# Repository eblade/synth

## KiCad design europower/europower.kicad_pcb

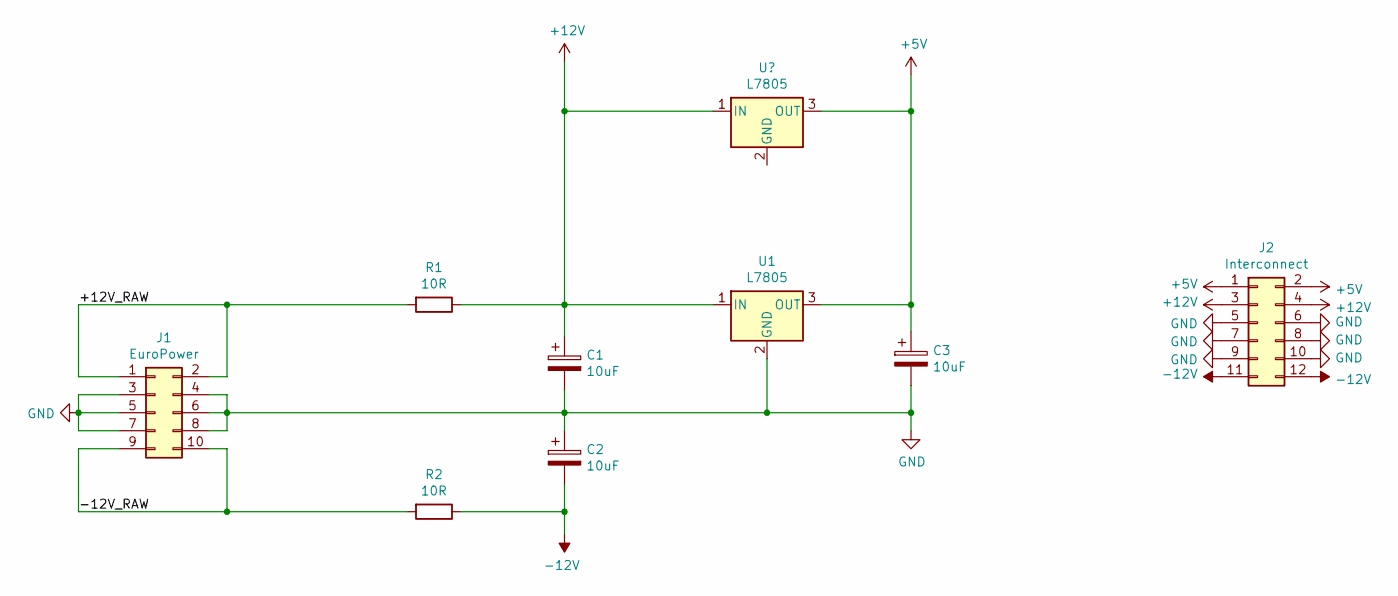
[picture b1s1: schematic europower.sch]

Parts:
C1, C2, C3: 10uF; CP_Radial_D5.0mm_P2.50mm
J1: EuroPower; PinHeader_2x05_P2.54mm_Vertical
J2: Interconnect; PinHeader_2x06_P2.54mm_Horizontal
R1, R2: 10R; R_Axial_DIN0207_L6.3mm_D2.5mm_P7.62mm_Horizontal
U1: L7805; TO-220-3_Horizontal_TabDown

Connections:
+5V: C3.1, J2.1, J2.2, U1.3 (OUT); also elsewhere on the board
+12V: C1.1, J2.3, J2.4, R1.1, U1.1 (IN); also elsewhere on the board
-12V: C2.2, J2.11, J2.12, R2.1
/+12V_RAW: J1.1, J1.2, R1.2
/-12V_RAW: J1.9, J1.10, R2.2
GND: C1.2, C2.1, C3.2, J1.3, J1.4, J1.5, J1.6, J1.7, J1.8, J2.5, J2.6, J2.7, J2.8, J2.9, J2.10, U1.2 (GND)

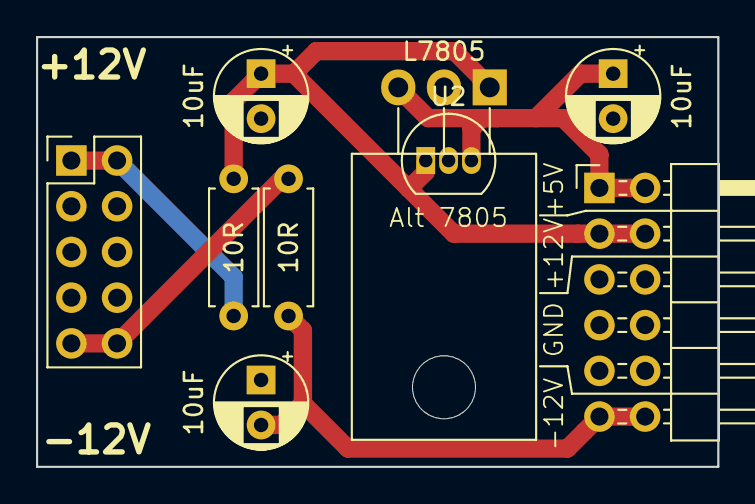
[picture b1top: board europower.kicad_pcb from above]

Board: 2 copper layers, 37.8 x 23.9 mm, 9 parts (0 on the bottom side), 6 nets.

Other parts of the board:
U2: L7805; TO-92_Inline

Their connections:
+5V: U2.3; also elsewhere on the board
+12V: U2.1; also elsewhere on the board

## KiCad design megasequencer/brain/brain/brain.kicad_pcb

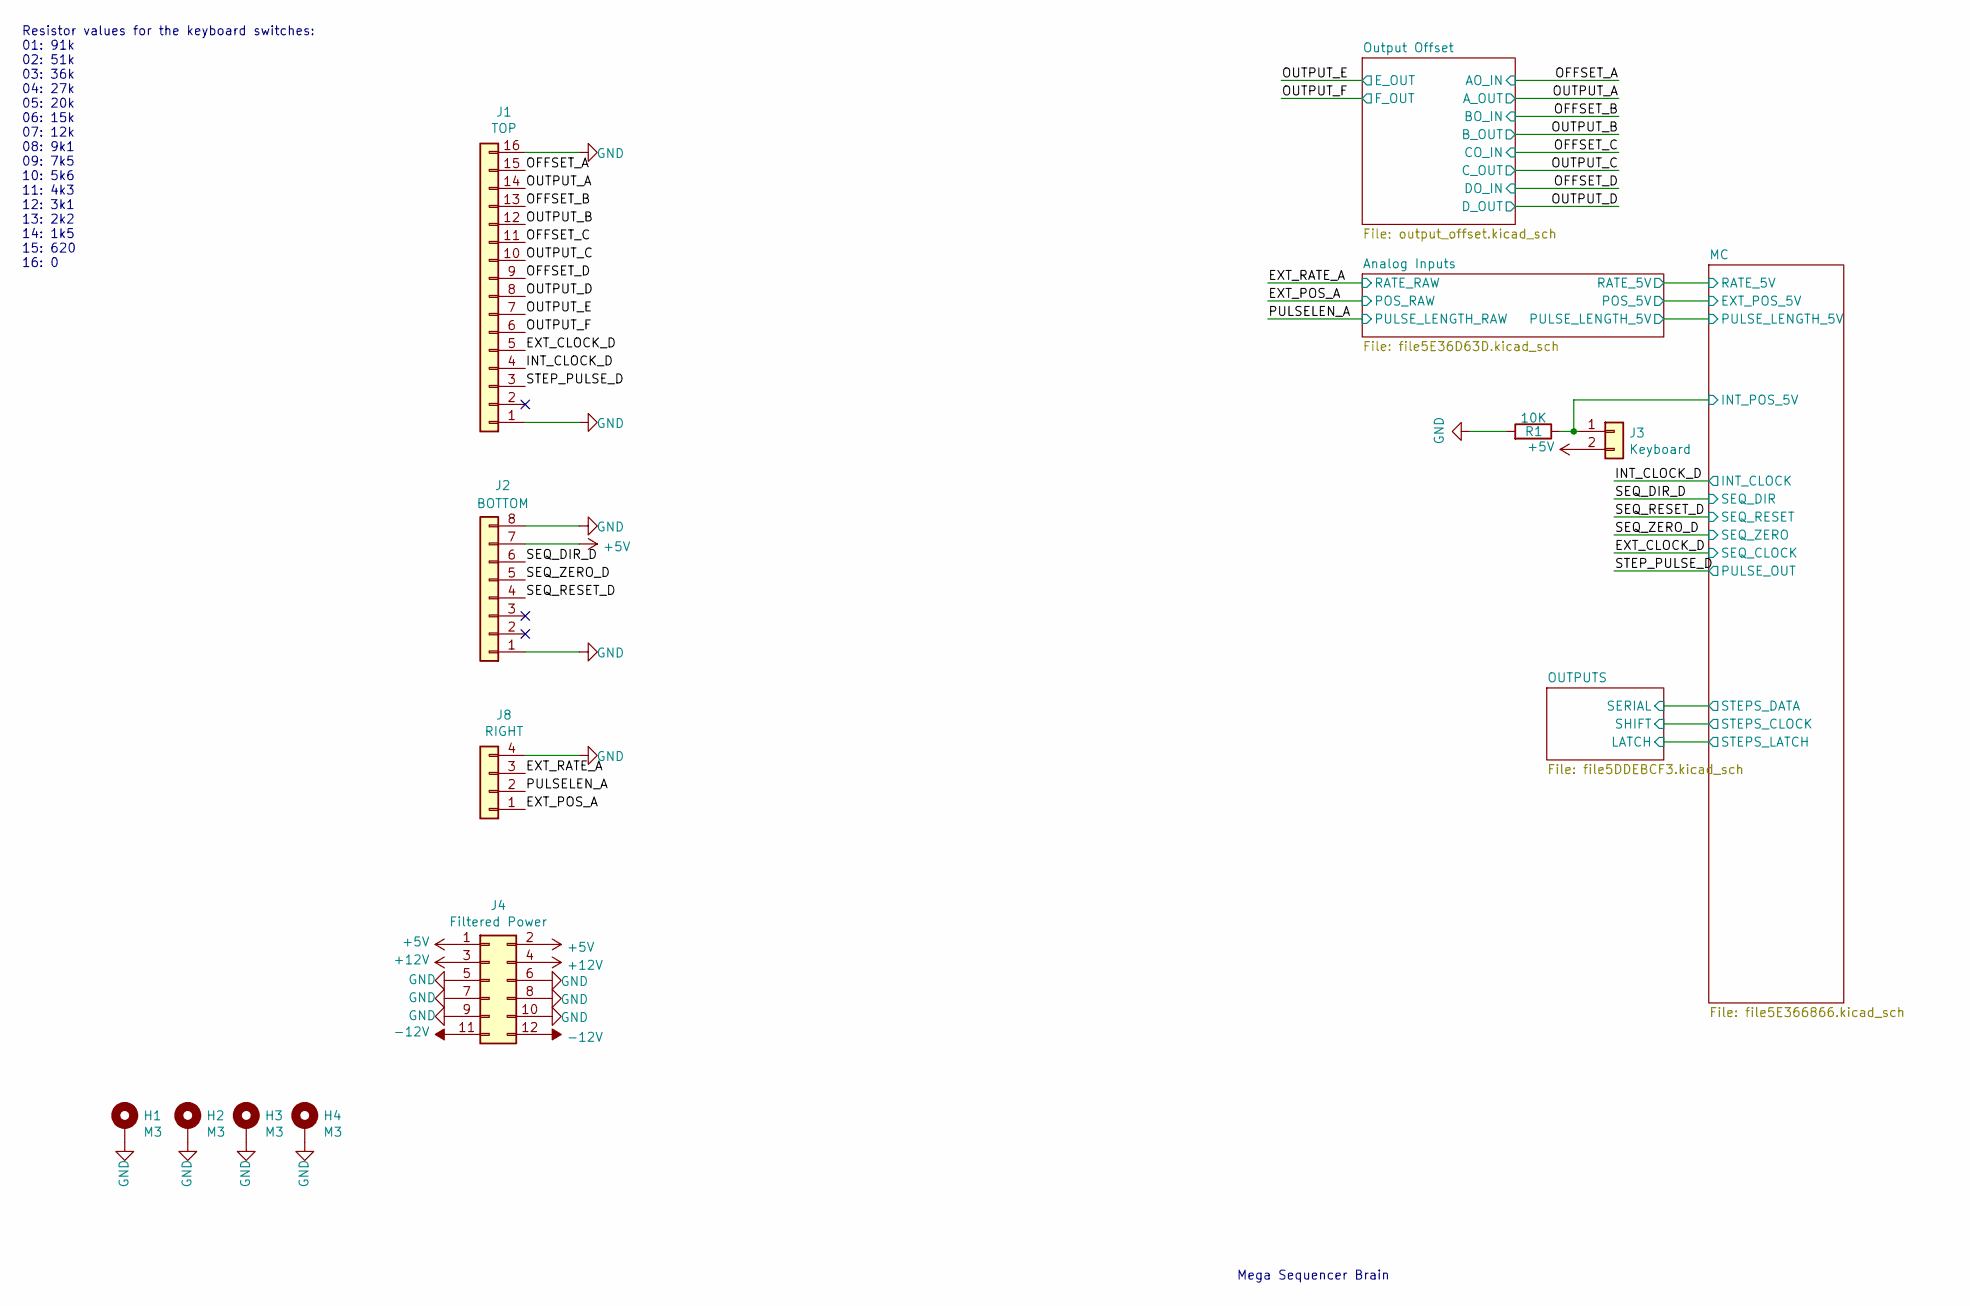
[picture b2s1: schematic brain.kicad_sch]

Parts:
H1, H2, H3, H4: M3; MountingHole_3.2mm_M3_Pad
J1: TOP; PinSocket_1x16_P2.54mm_Vertical
J2: BOTTOM; PinSocket_1x08_P2.54mm_Vertical
J3: Keyboard; PinHeader_1x02_P2.54mm_Vertical
J4: Filtered Power; PinHeader_2x06_P2.54mm_Vertical
J8: RIGHT; PinSocket_1x04_P2.54mm_Vertical
R1: 10K; R_Axial_DIN0207_L6.3mm_D2.5mm_P7.62mm_Horizontal

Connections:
+5V: J2.7, J3.2, J4.1, J4.2; also elsewhere on the board
+12V: J4.3, J4.4; also elsewhere on the board
-12V: J4.11, J4.12; also elsewhere on the board
/EXT_CLOCK_D: J1.5; also elsewhere on the board
/EXT_POS_A: J8.1; also elsewhere on the board
/EXT_RATE_A: J8.3; also elsewhere on the board
/INT_CLOCK_D: J1.4; also elsewhere on the board
/MC/INT_POS_5V: J3.1, R1.1; also elsewhere on the board
/OFFSET_A: J1.15; also elsewhere on the board
/OFFSET_B: J1.13; also elsewhere on the board
/OFFSET_C: J1.11; also elsewhere on the board
/OFFSET_D: J1.9; also elsewhere on the board
/OUTPUT_A: J1.14; also elsewhere on the board
/OUTPUT_B: J1.12; also elsewhere on the board
/OUTPUT_C: J1.10; also elsewhere on the board
/OUTPUT_D: J1.8; also elsewhere on the board
/OUTPUT_E: J1.7; also elsewhere on the board
/OUTPUT_F: J1.6; also elsewhere on the board
/PULSELEN_A: J8.2; also elsewhere on the board
/SEQ_DIR_D: J2.6; also elsewhere on the board
/SEQ_RESET_D: J2.4; also elsewhere on the board
/SEQ_ZERO_D: J2.5; also elsewhere on the board
/STEP_PULSE_D: J1.3; also elsewhere on the board
GND: H1.1, H2.1, H3.1, H4.1, J1.1, J1.16, J2.1, J2.8, J4.5, J4.6, J4.7, J4.8, J4.9, J4.10, J8.4, R1.2; also elsewhere on the board

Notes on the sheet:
Resistor values for the keyboard switches: 01: 91k 02: 51k 03: 36k 04: 27k 05: 20k 06: 15k 07: 12k 08: 9k1 09: 7k5 10: 5k6 11: 4k3 12: 3k1 13: 2k2 14: 1k5 15: 620 16: 0
Mega Sequencer Brain

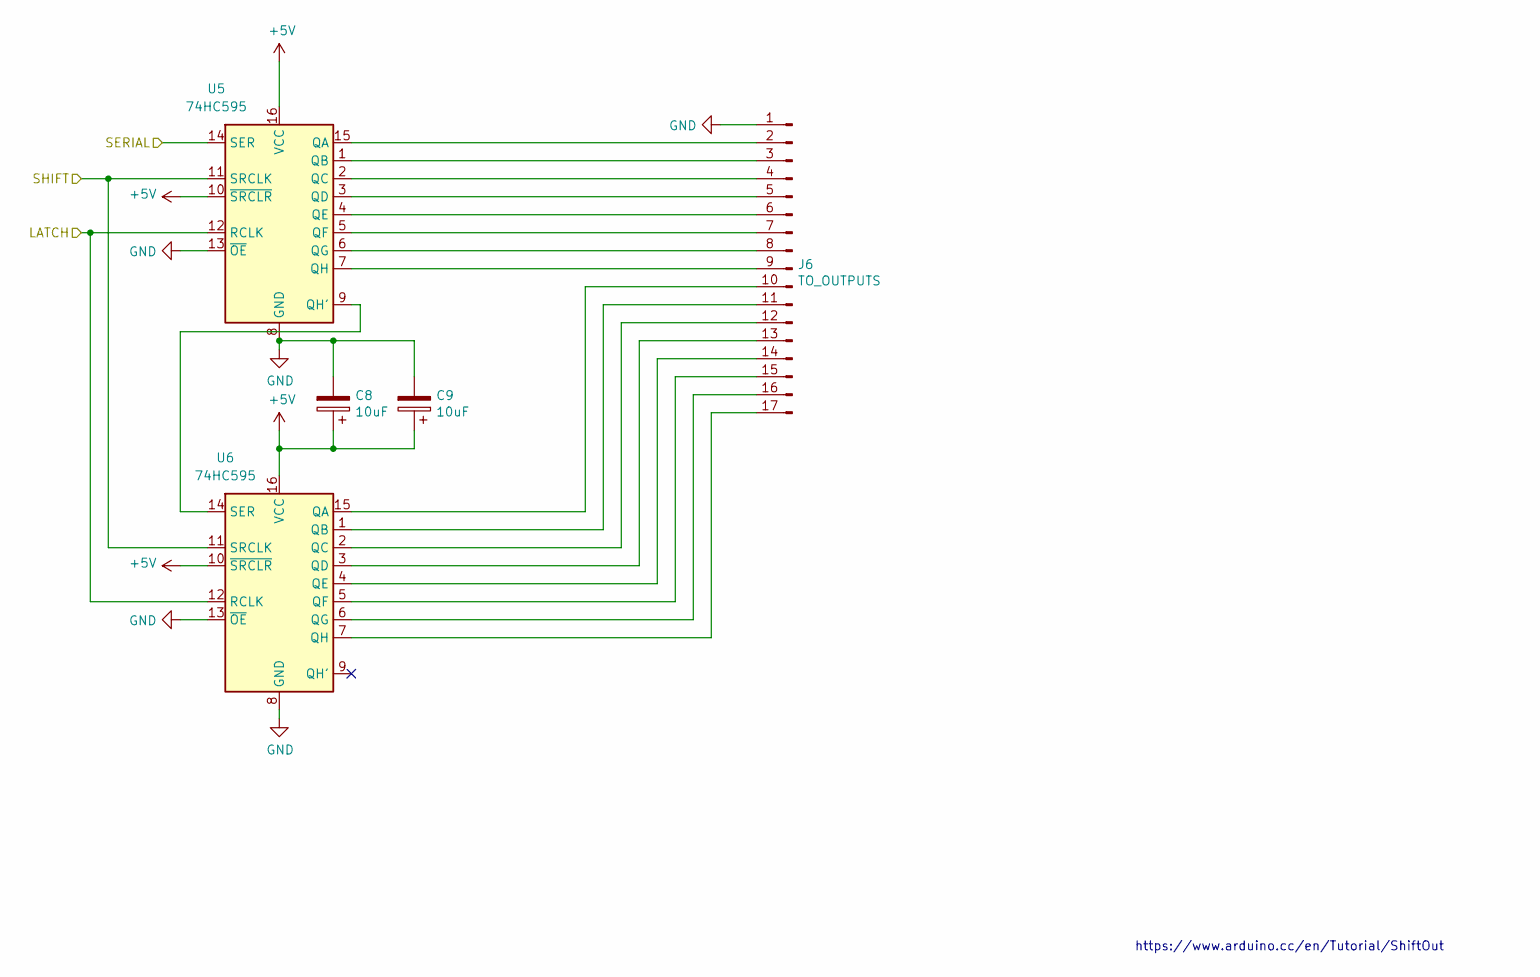
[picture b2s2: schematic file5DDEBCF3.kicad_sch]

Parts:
C8, C9: 10uF; CP_Radial_D5.0mm_P2.00mm
J6: TO_OUTPUTS; PinHeader_1x17_P2.54mm_Vertical
U5, U6: 74HC595; DIP-16_W7.62mm

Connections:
+5V: C8.1, C9.1, U5.10 (~SRCLR), U5.16 (VCC), U6.10 (~SRCLR), U6.16 (VCC); also elsewhere on the board
/OUTPUTS/LATCH: U5.12 (RCLK), U6.12 (RCLK); also elsewhere on the board
/OUTPUTS/SERIAL: U5.14 (SER); also elsewhere on the board
/OUTPUTS/SHIFT: U5.11 (SRCLK), U6.11 (SRCLK); also elsewhere on the board
GND: C8.2, C9.2, J6.1, U5.8 (GND), U5.13 (~OE), U6.8 (GND), U6.13 (~OE); also elsewhere on the board
unnamed: J6.2, U5.15 (QA)
unnamed: J6.3, U5.1 (QB)
unnamed: J6.4, U5.2 (QC)
unnamed: J6.5, U5.3 (QD)
unnamed: J6.6, U5.4 (QE)
unnamed: J6.7, U5.5 (QF)
unnamed: J6.8, U5.6 (QG)
unnamed: J6.9, U5.7 (QH)
unnamed: J6.10, U6.15 (QA)
unnamed: J6.11, U6.1 (QB)
unnamed: J6.12, U6.2 (QC)
unnamed: J6.13, U6.3 (QD)
unnamed: J6.14, U6.4 (QE)
unnamed: J6.15, U6.5 (QF)
unnamed: J6.16, U6.6 (QG)
unnamed: J6.17, U6.7 (QH)
unnamed: U5.9 (QH'), U6.14 (SER)

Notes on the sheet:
https://www.arduino.cc/en/Tutorial/ShiftOut

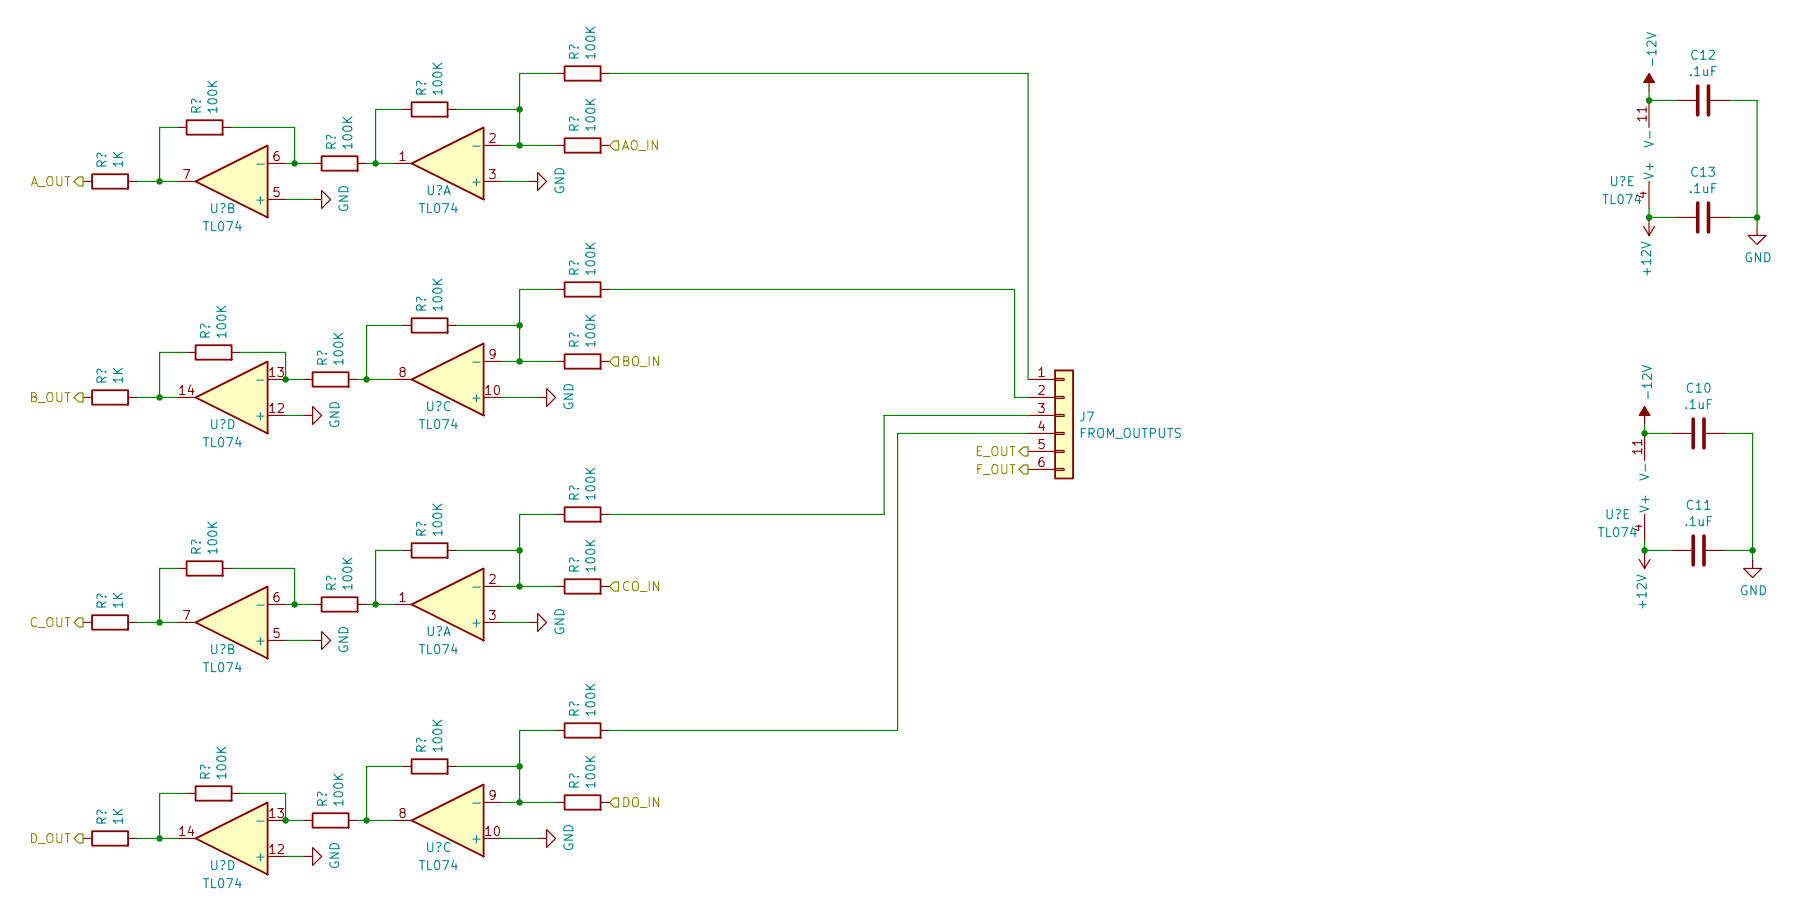
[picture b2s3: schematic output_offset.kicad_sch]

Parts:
C10, C11, C12, C13: .1uF; C_Disc_D3.0mm_W1.6mm_P2.50mm
J7: FROM_OUTPUTS; PinHeader_1x06_P2.54mm_Vertical
R16, R17, R18, R19: 1K; R_Axial_DIN0207_L6.3mm_D2.5mm_P7.62mm_Horizontal
R20, R21, R22, R23, R24, R25, R26, R27, R28, R29, R30, R31, R32, R33, R34, R35, R36, R37, R38, R39: 100K; R_Axial_DIN0207_L6.3mm_D2.5mm_P7.62mm_Horizontal
U7, U8: TL074; DIP-14_W7.62mm

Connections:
+12V: C11.2, C13.2, U7.4 (V+), U8.4 (V+); also elsewhere on the board
-12V: C10.2, C12.2, U7.11 (V-), U8.11 (V-); also elsewhere on the board
/OFFSET_A: R33.2; also elsewhere on the board
/OFFSET_B: R35.2; also elsewhere on the board
/OFFSET_C: R37.2; also elsewhere on the board
/OFFSET_D: R39.2; also elsewhere on the board
/OUTPUT_A: R16.1; also elsewhere on the board
/OUTPUT_B: R17.1; also elsewhere on the board
/OUTPUT_C: R18.1; also elsewhere on the board
/OUTPUT_D: R19.1; also elsewhere on the board
/OUTPUT_E: J7.5; also elsewhere on the board
/OUTPUT_F: J7.6; also elsewhere on the board
GND: C10.1, C11.1, C12.1, C13.1, U7.3 (+), U7.5 (+), U7.10 (+), U7.12 (+), U8.3 (+), U8.5 (+), U8.10 (+), U8.12 (+); also elsewhere on the board
unnamed: J7.1, R32.2
unnamed: J7.2, R34.2
unnamed: J7.3, R36.2
unnamed: J7.4, R38.2
unnamed: R16.2, R20.1, U7.7
unnamed: R17.2, R22.1, U7.14
unnamed: R18.2, R21.1, U8.7
unnamed: R19.2, R23.1, U8.14
unnamed: R20.2, R26.1, U7.6 (-)
unnamed: R21.2, R27.1, U8.6 (-)
unnamed: R22.2, R24.1, U7.13 (-)
unnamed: R23.2, R25.1, U8.13 (-)
unnamed: R24.2, R29.1, U7.8
unnamed: R25.2, R31.1, U8.8
unnamed: R26.2, R28.1, U7.1
unnamed: R27.2, R30.1, U8.1
unnamed: R28.2, R32.1, R33.1, U7.2 (-)
unnamed: R29.2, R34.1, R35.1, U7.9 (-)
unnamed: R30.2, R36.1, R37.1, U8.2 (-)
unnamed: R31.2, R38.1, R39.1, U8.9 (-)

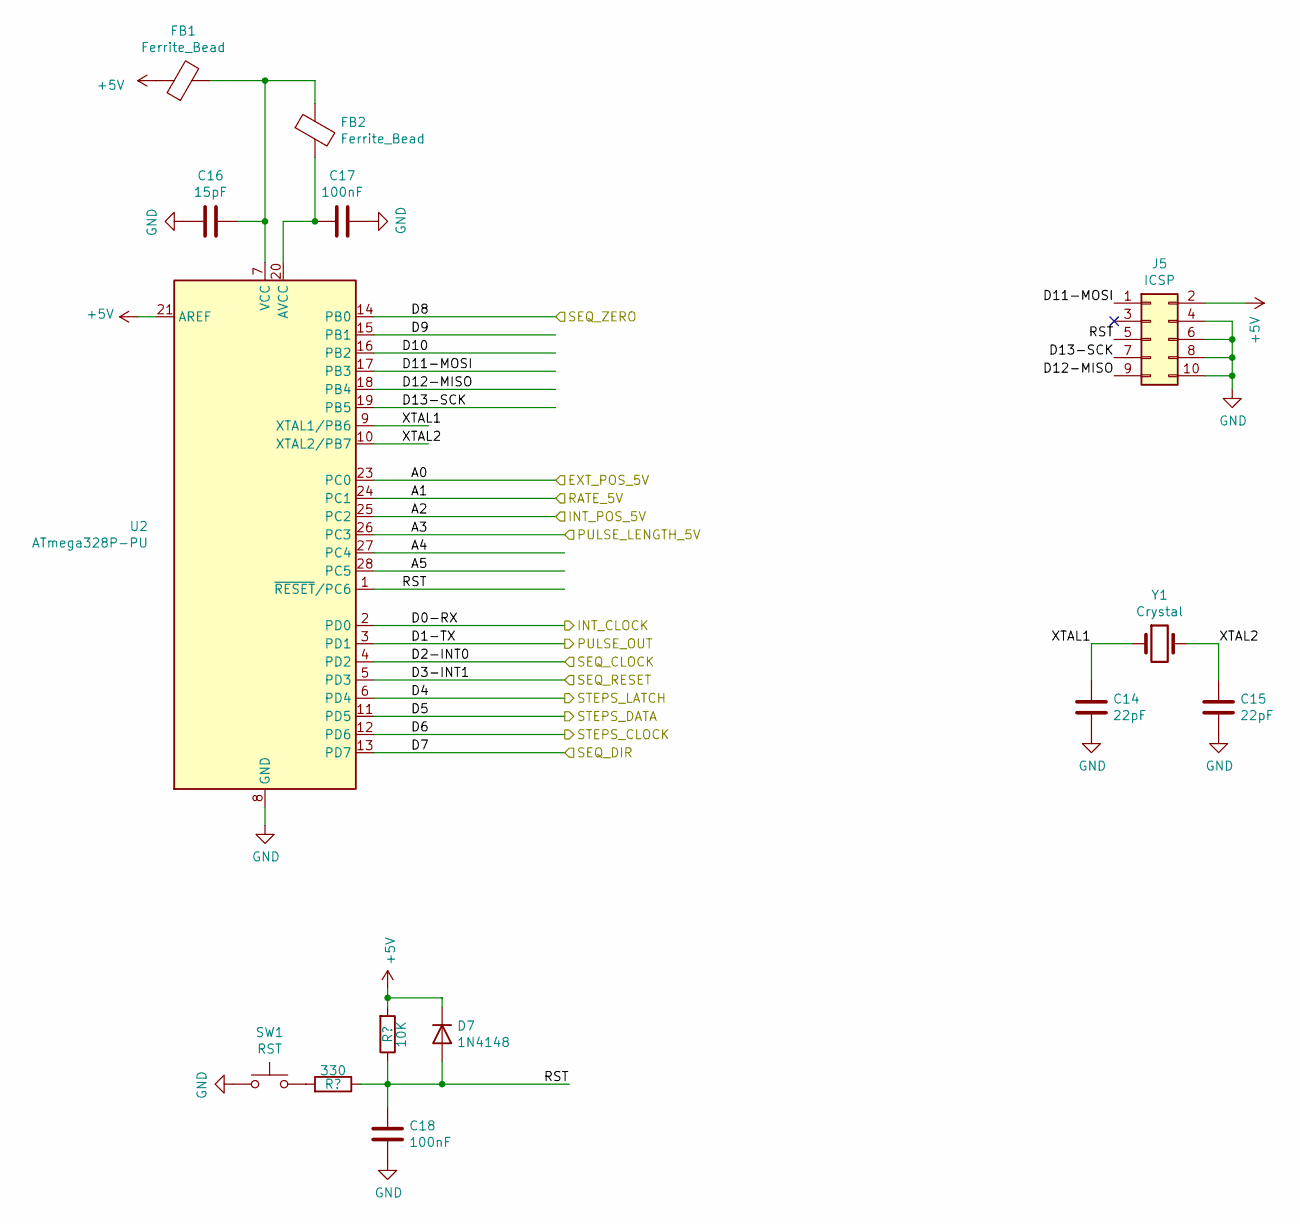
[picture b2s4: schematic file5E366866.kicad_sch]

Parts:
C14, C15: 22pF; C_Disc_D3.0mm_W1.6mm_P2.50mm
C16: 15pF; C_Disc_D3.0mm_W1.6mm_P2.50mm
C17, C18: 100nF; C_Disc_D3.0mm_W1.6mm_P2.50mm
D7: 1N4148; D_A-405_P7.62mm_Horizontal
FB1, FB2: Ferrite_Bead; L_Axial_L6.6mm_D2.7mm_P10.16mm_Horizontal_Vishay_IM-2
J5: ICSP; PinHeader_2x05_P2.54mm_Vertical
R40: 330; R_Axial_DIN0207_L6.3mm_D2.5mm_P7.62mm_Horizontal
R41: 10K; R_Axial_DIN0207_L6.3mm_D2.5mm_P7.62mm_Horizontal
SW1: RST; SW_PUSH_6mm
U2: ATmega328P-PU; DIP-28_W7.62mm
Y1: Crystal; Crystal_HC18-U_Vertical

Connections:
+5V: D7.1 (K), FB1.1, J5.2, R41.2, U2.21 (AREF); also elsewhere on the board
/Analog Inputs/PULSE_LENGTH_5V: U2.26 (PC3); also elsewhere on the board
/Analog Inputs/RATE_5V: U2.24 (PC1); also elsewhere on the board
/EXT_CLOCK_D: U2.4 (PD2); also elsewhere on the board
/INT_CLOCK_D: U2.2 (PD0); also elsewhere on the board
/MC/A4: U2.27 (PC4)
/MC/A5: U2.28 (PC5)
/MC/D9: U2.15 (PB1)
/MC/D10: U2.16 (PB2)
/MC/D11-MOSI: J5.1, U2.17 (PB3)
/MC/D12-MISO: J5.9, U2.18 (PB4)
/MC/D13-SCK: J5.7, U2.19 (PB5)
/MC/EXT_POS_5V: U2.23 (PC0); also elsewhere on the board
/MC/INT_POS_5V: U2.25 (PC2); also elsewhere on the board
/MC/RST: C18.1, D7.2 (A), J5.5, R40.1, R41.1, U2.1 (~RESET/PC6)
/MC/XTAL1: C14.1, U2.9 (XTAL1/PB6), Y1.1
/MC/XTAL2: C15.1, U2.10 (XTAL2/PB7), Y1.2
/OUTPUTS/LATCH: U2.6 (PD4); also elsewhere on the board
/OUTPUTS/SERIAL: U2.11 (PD5); also elsewhere on the board
/OUTPUTS/SHIFT: U2.12 (PD6); also elsewhere on the board
/SEQ_DIR_D: U2.13 (PD7); also elsewhere on the board
/SEQ_RESET_D: U2.5 (PD3); also elsewhere on the board
/SEQ_ZERO_D: U2.14 (PB0); also elsewhere on the board
/STEP_PULSE_D: U2.3 (PD1); also elsewhere on the board
GND: C14.2, C15.2, C16.1, C17.1, C18.2, J5.4, J5.6, J5.8, J5.10, SW1.1, U2.8 (GND), U2.22 (GND); also elsewhere on the board
unnamed: C16.2, FB1.2, FB2.1, U2.7 (VCC)
unnamed: C17.2, FB2.2, U2.20 (AVCC)
unnamed: R40.2, SW1.2

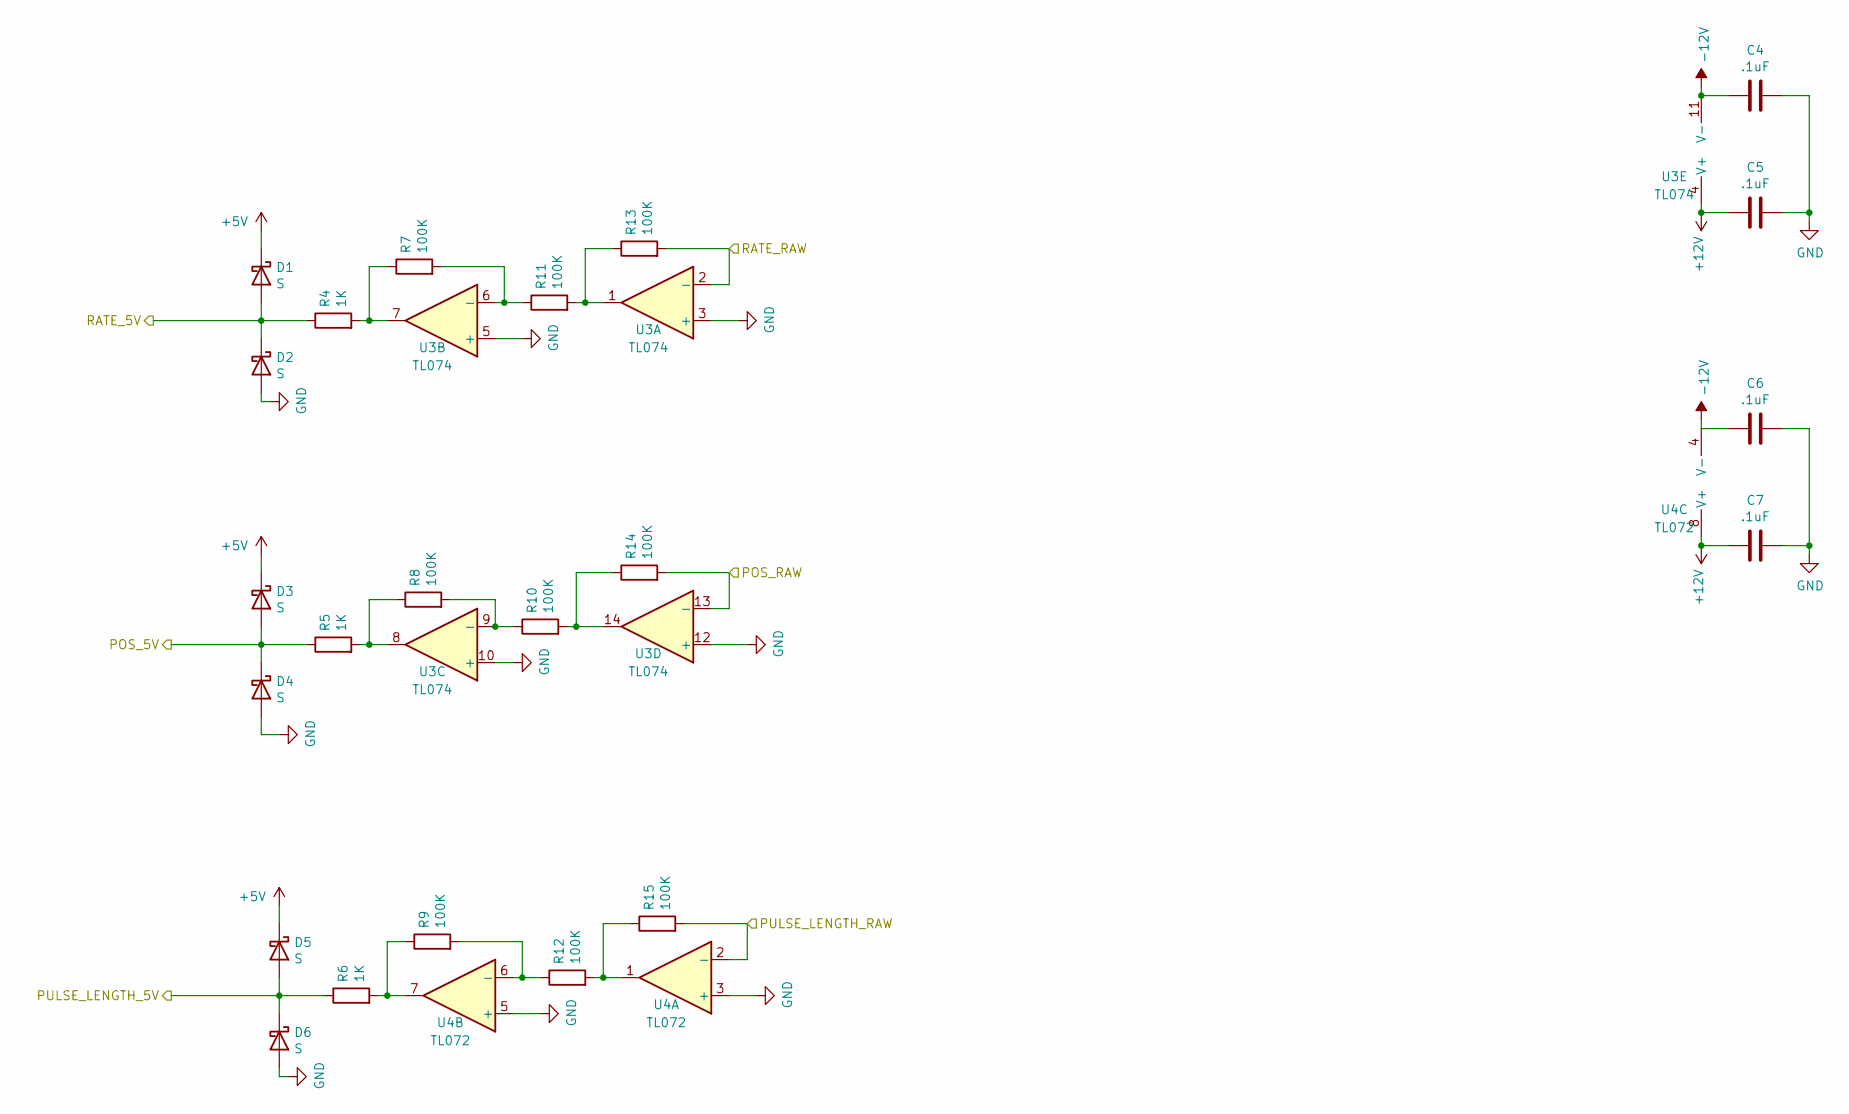
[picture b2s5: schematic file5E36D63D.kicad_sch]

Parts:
C4, C5, C6, C7: .1uF; C_Disc_D3.0mm_W1.6mm_P2.50mm
D1, D2, D3, D4, D5, D6: S; D_DO-34_SOD68_P7.62mm_Horizontal
R4, R5, R6: 1K; R_Axial_DIN0207_L6.3mm_D2.5mm_P7.62mm_Horizontal
R7, R8, R9, R10, R11, R12, R13, R14, R15: 100K; R_Axial_DIN0207_L6.3mm_D2.5mm_P7.62mm_Horizontal
U3: TL074; DIP-14_W7.62mm
U4: TL072; DIP-8_W7.62mm

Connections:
+5V: D1.1 (K), D3.1 (K), D5.1 (K); also elsewhere on the board
+12V: C5.2, C7.2, U3.4 (V+), U4.8 (V+); also elsewhere on the board
-12V: C4.2, C6.2, U3.11 (V-), U4.4 (V-); also elsewhere on the board
/Analog Inputs/PULSE_LENGTH_5V: D5.2 (A), D6.1 (K), R6.1; also elsewhere on the board
/Analog Inputs/RATE_5V: D1.2 (A), D2.1 (K), R4.1; also elsewhere on the board
/EXT_POS_A: R14.2, U3.13 (-); also elsewhere on the board
/EXT_RATE_A: R13.2, U3.2 (-); also elsewhere on the board
/MC/EXT_POS_5V: D3.2 (A), D4.1 (K), R5.1; also elsewhere on the board
/PULSELEN_A: R15.2, U4.2 (-); also elsewhere on the board
GND: C4.1, C5.1, C6.1, C7.1, D2.2 (A), D4.2 (A), D6.2 (A), U3.3 (+), U3.5 (+), U3.10 (+), U3.12 (+), U4.3 (+), U4.5 (+); also elsewhere on the board
unnamed: R4.2, R7.1, U3.7
unnamed: R5.2, R8.1, U3.8
unnamed: R6.2, R9.1, U4.7
unnamed: R8.2, R10.1, U3.9 (-)
unnamed: R10.2, R14.1, U3.14
unnamed: R7.2, R11.1, U3.6 (-)
unnamed: R11.2, R13.1, U3.1
unnamed: R9.2, R12.1, U4.6 (-)
unnamed: R12.2, R15.1, U4.1

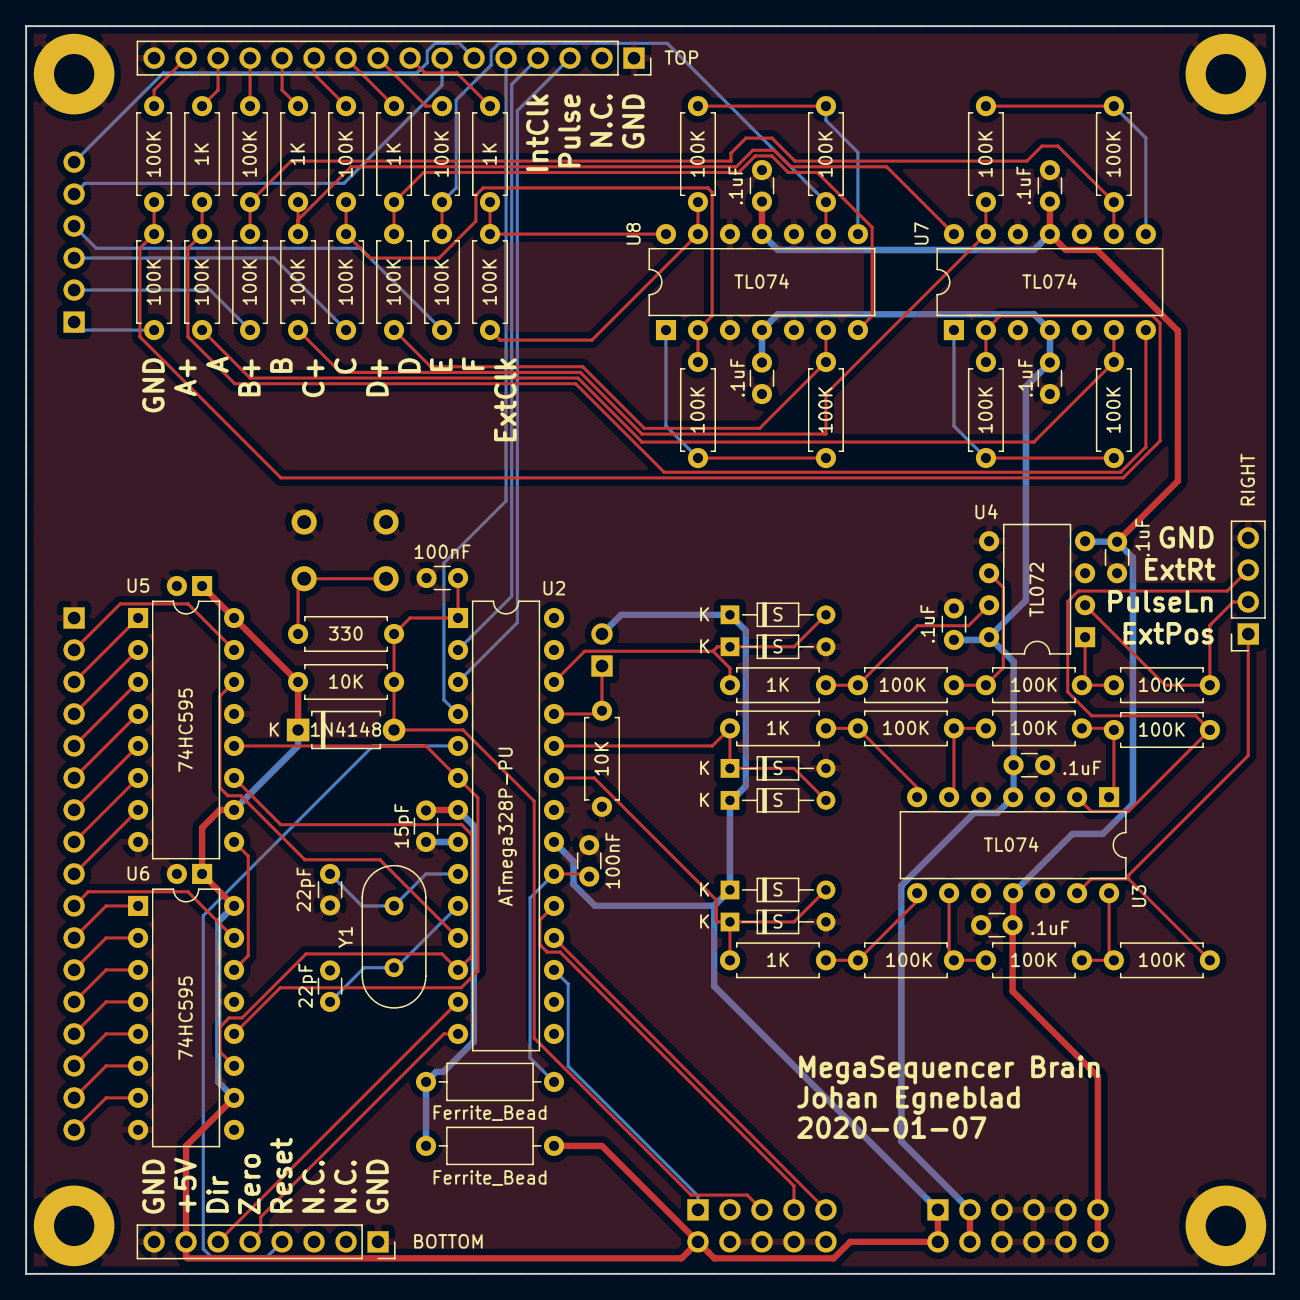
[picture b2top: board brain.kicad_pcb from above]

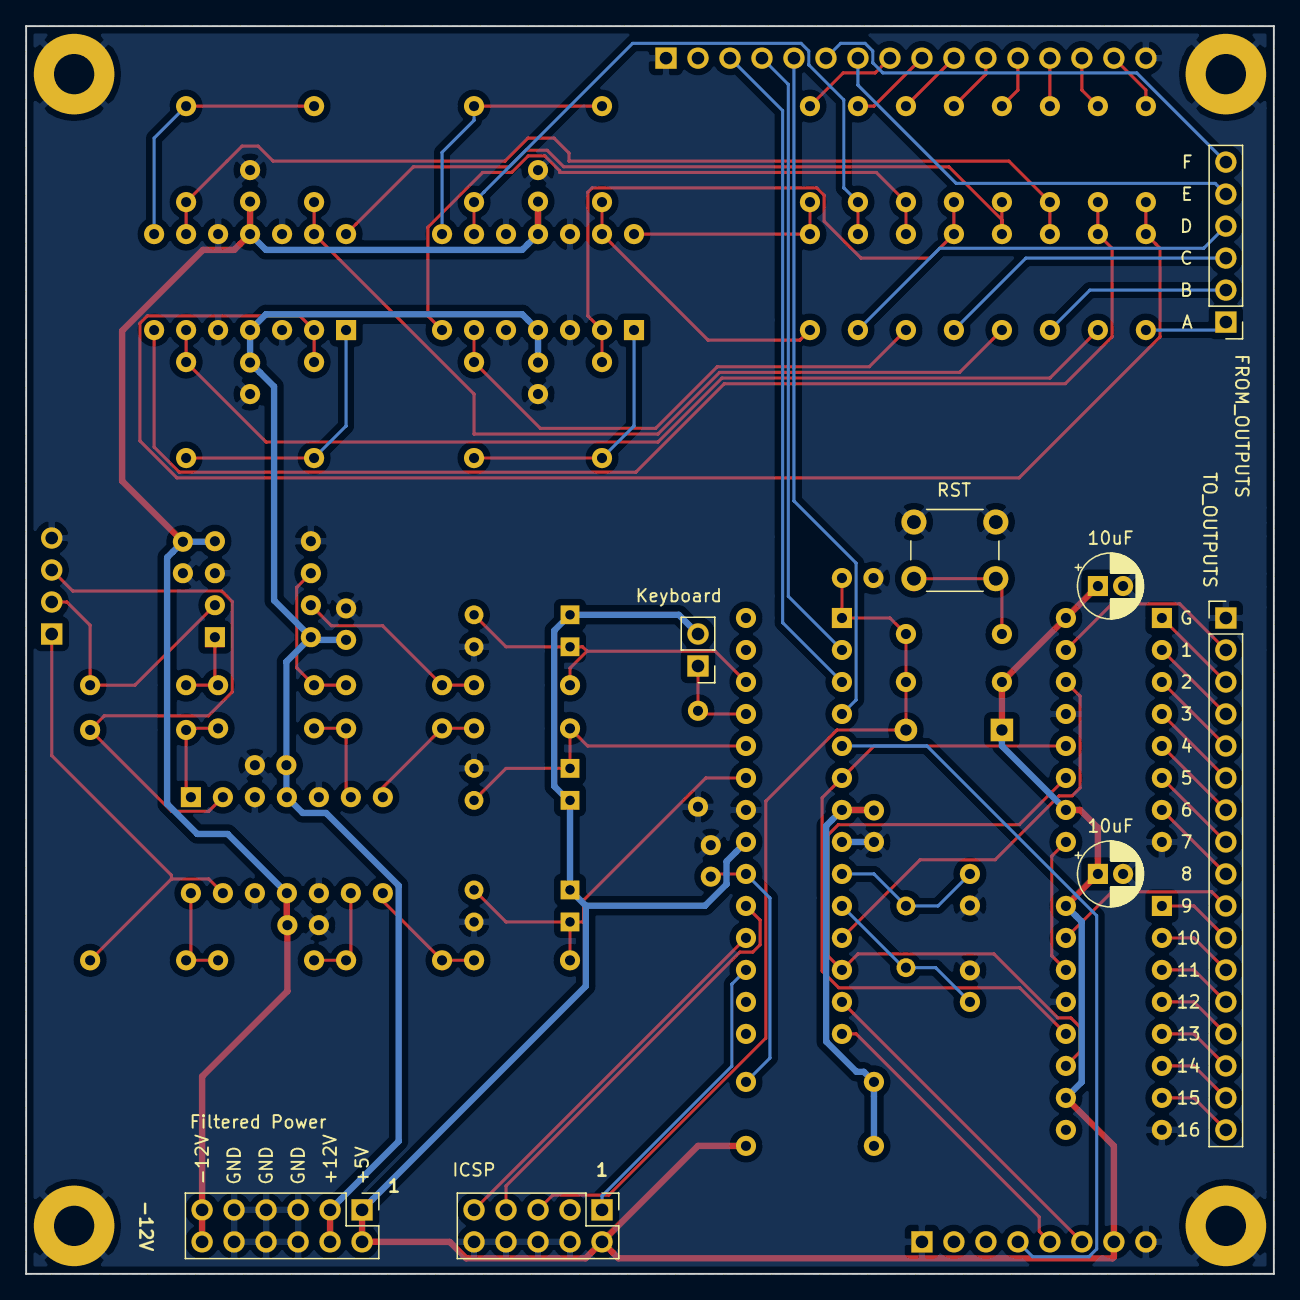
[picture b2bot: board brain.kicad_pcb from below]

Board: 2 copper layers, 99.1 x 99.1 mm, 84 parts (8 on the bottom side), 85 nets.

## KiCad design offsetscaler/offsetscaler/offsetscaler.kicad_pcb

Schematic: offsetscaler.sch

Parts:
C1, C2: 10uF; CP_Radial_D4.0mm_P2.00mm
D1, D3: GREEN; LED_D5.0mm
D2, D4: RED; LED_D5.0mm
J1: IN 1; Jack_3.5mm_QingPu_WQP-PJ398SM_Vertical_CircularHoles
J2: OUT 1; Jack_3.5mm_QingPu_WQP-PJ398SM_Vertical_CircularHoles
J3: INV OUT 1; Jack_3.5mm_QingPu_WQP-PJ398SM_Vertical_CircularHoles
J4: EURO_PWR_2x5; PinSocket_2x05_P2.54mm_Vertical
J5: IN 2; Jack_3.5mm_QingPu_WQP-PJ398SM_Vertical_CircularHoles
J6: OUT 2; Jack_3.5mm_QingPu_WQP-PJ398SM_Vertical_CircularHoles
J7: INV OUT 2; Jack_3.5mm_QingPu_WQP-PJ398SM_Vertical_CircularHoles
R1, R2, R3, R4, R12, R13, R15, R16: 10k; R_Axial_DIN0207_L6.3mm_D2.5mm_P7.62mm_Horizontal
R5, R6, R9, R10, R17, R18, R19, R20: 1k; R_Axial_DIN0207_L6.3mm_D2.5mm_P7.62mm_Horizontal
R7, R8, R11, R14: 100K; Potentiometer_Alps_RK09L_Single_Vertical
U1: TL074; DIP-14_W7.62mm_LongPads

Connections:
+12V: C2.1, J4.1, J4.2, R8.1, R11.1, U1.4 (V+)
-12V: C1.2, J4.9, J4.10, R8.3, R11.3, U1.11 (V-)
GND: C1.1, C2.2, D1.1 (K), D2.2 (A), D3.1 (K), D4.2 (A), J1.S, J1.SN, J2.S, J2.SN, J3.S, J3.SN, J4.3, J4.4, J4.5, J4.6, J4.7, J4.8, J5.S, J5.SN, J6.S, J6.SN, J7.S, J7.SN, U1.3 (+), U1.5 (+), U1.10 (+), U1.12 (+)
unnamed: D1.2 (A), R9.1
unnamed: D2.1 (K), R10.1
unnamed: D3.2 (A), R17.1
unnamed: D4.1 (K), R18.1
unnamed: J1.T, R1.2
unnamed: J2.T, R5.1
unnamed: J3.T, R6.1
unnamed: J5.T, R12.2
unnamed: J6.T, R19.1
unnamed: J7.T, R20.1
unnamed: R1.1, R2.1, R7.3, U1.2 (-)
unnamed: R2.2, R8.2
unnamed: R3.1, R4.2, U1.6 (-)
unnamed: R3.2, R6.2, R7.1, R7.2, U1.1
unnamed: R4.1, R5.2, R9.2, R10.2, U1.7
unnamed: R11.2, R13.2
unnamed: R12.1, R13.1, R14.3, U1.9 (-)
unnamed: R14.1, R14.2, R15.2, R20.2, U1.8
unnamed: R15.1, R16.2, U1.13 (-)
unnamed: R16.1, R17.2, R18.2, R19.2, U1.14

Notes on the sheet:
CV Offset Scaler

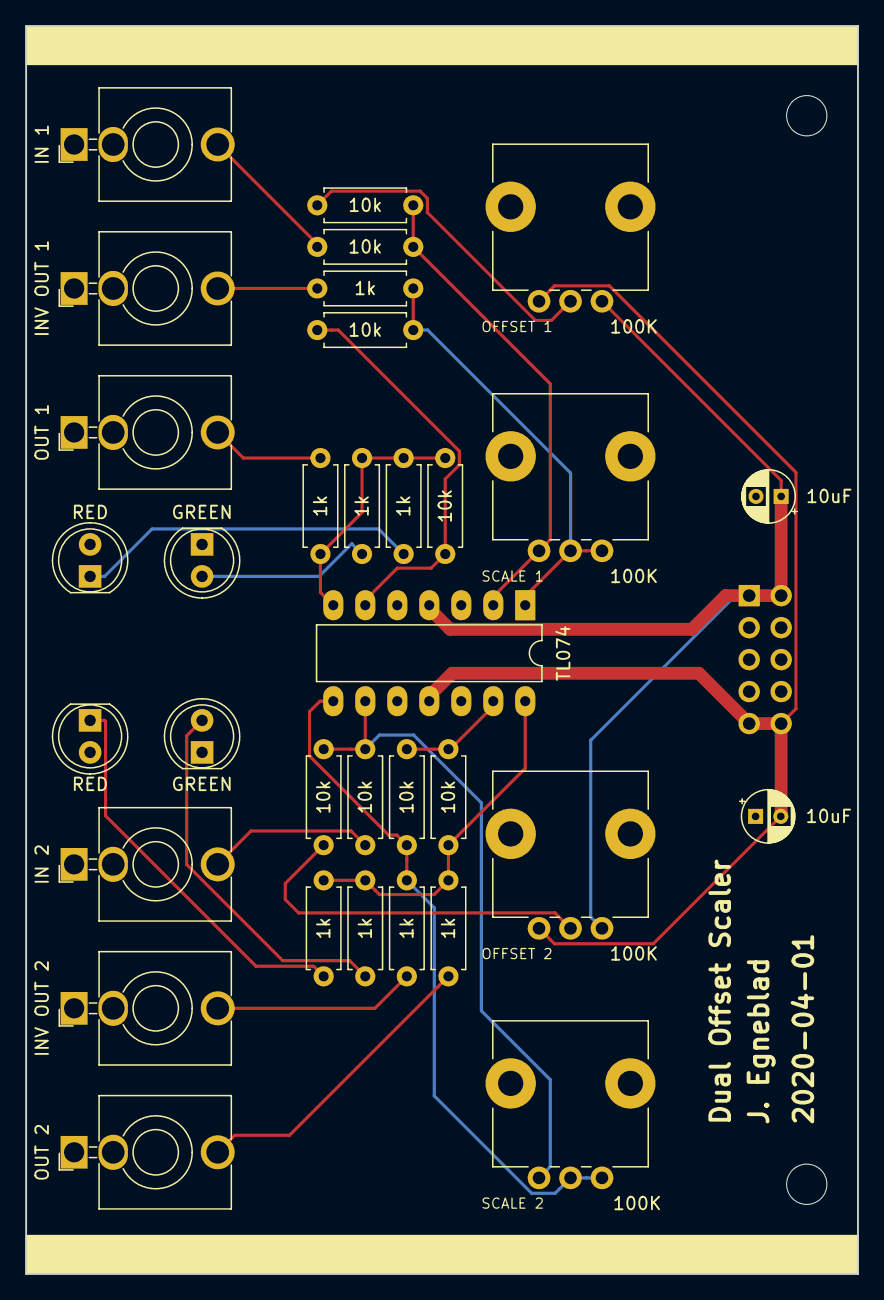
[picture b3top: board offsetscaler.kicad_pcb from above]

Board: 2 copper layers, 66.0 x 99.1 mm, 36 parts (1 on the bottom side), 23 nets.

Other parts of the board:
H1, H2: MountingHole; MountingHole_3.2mm_M3
